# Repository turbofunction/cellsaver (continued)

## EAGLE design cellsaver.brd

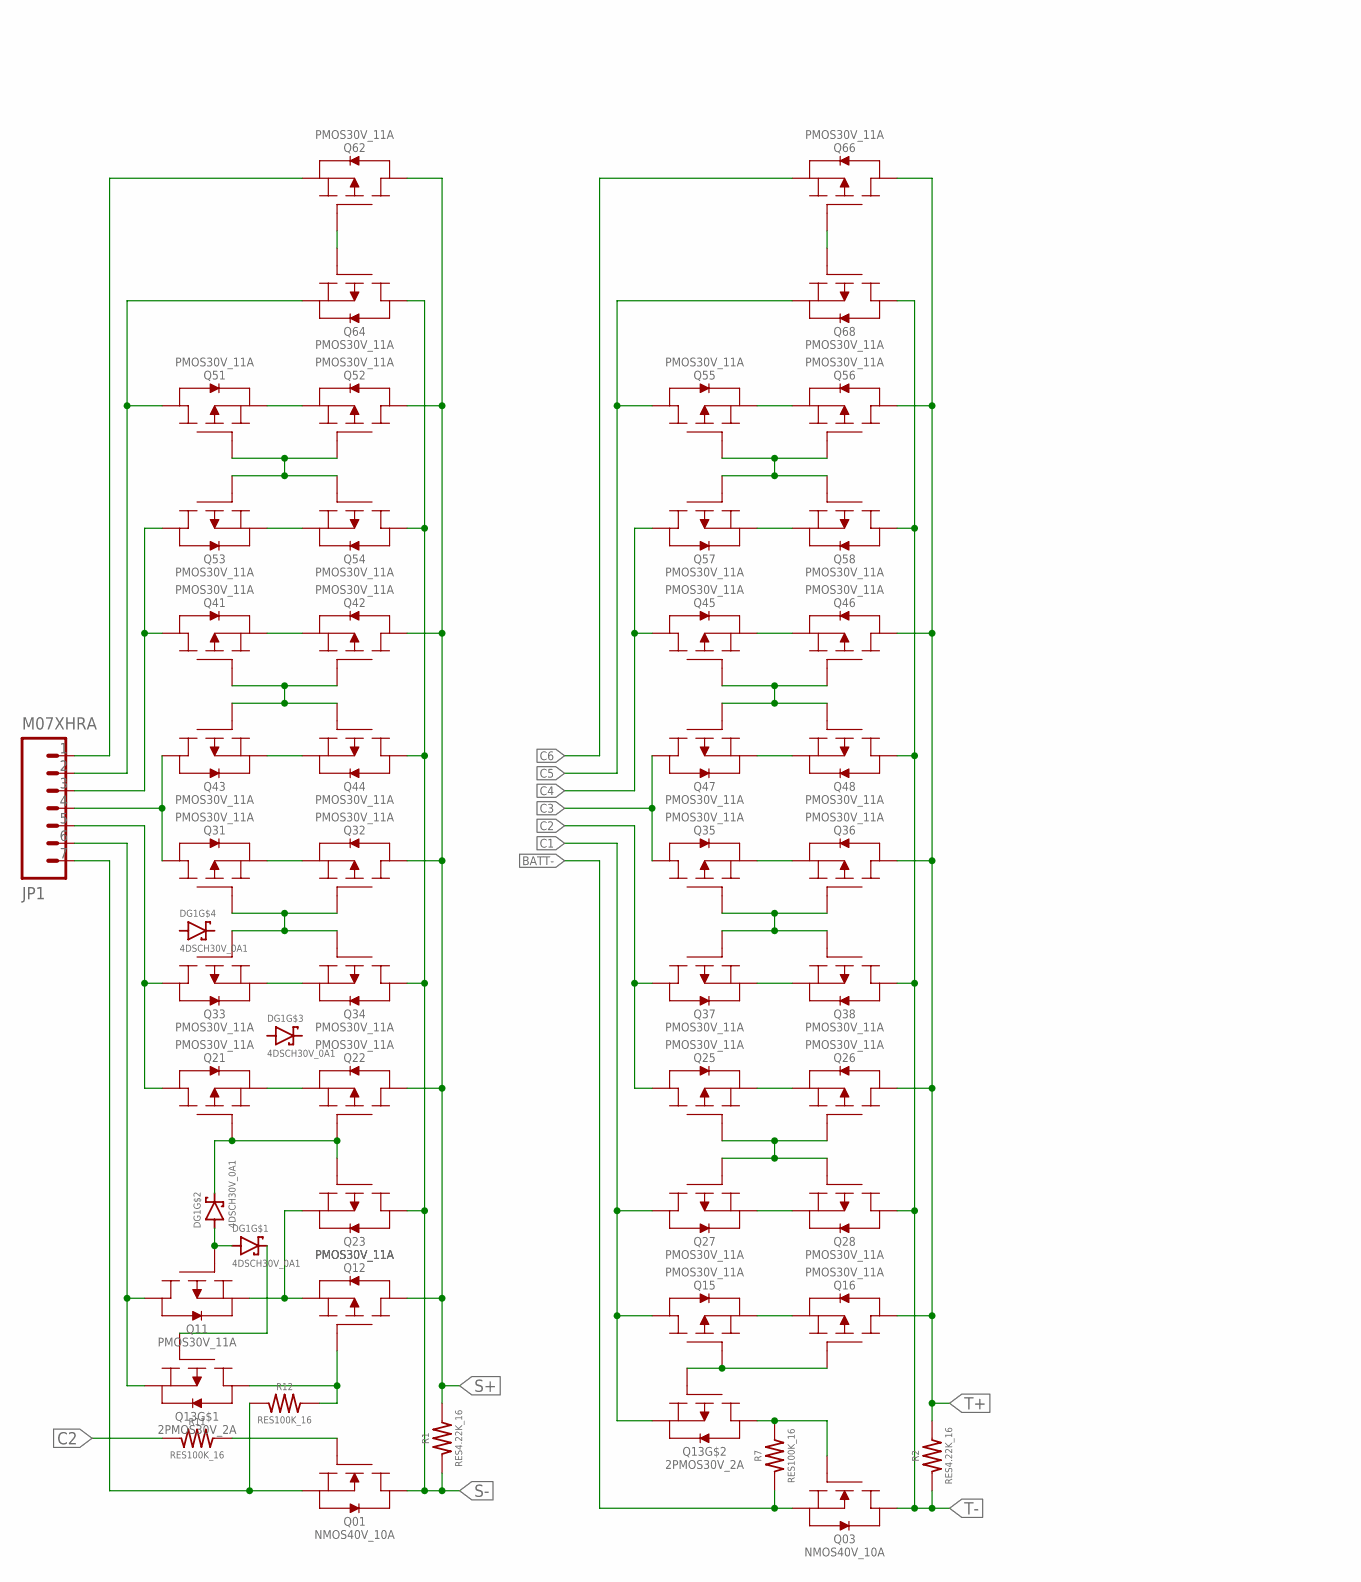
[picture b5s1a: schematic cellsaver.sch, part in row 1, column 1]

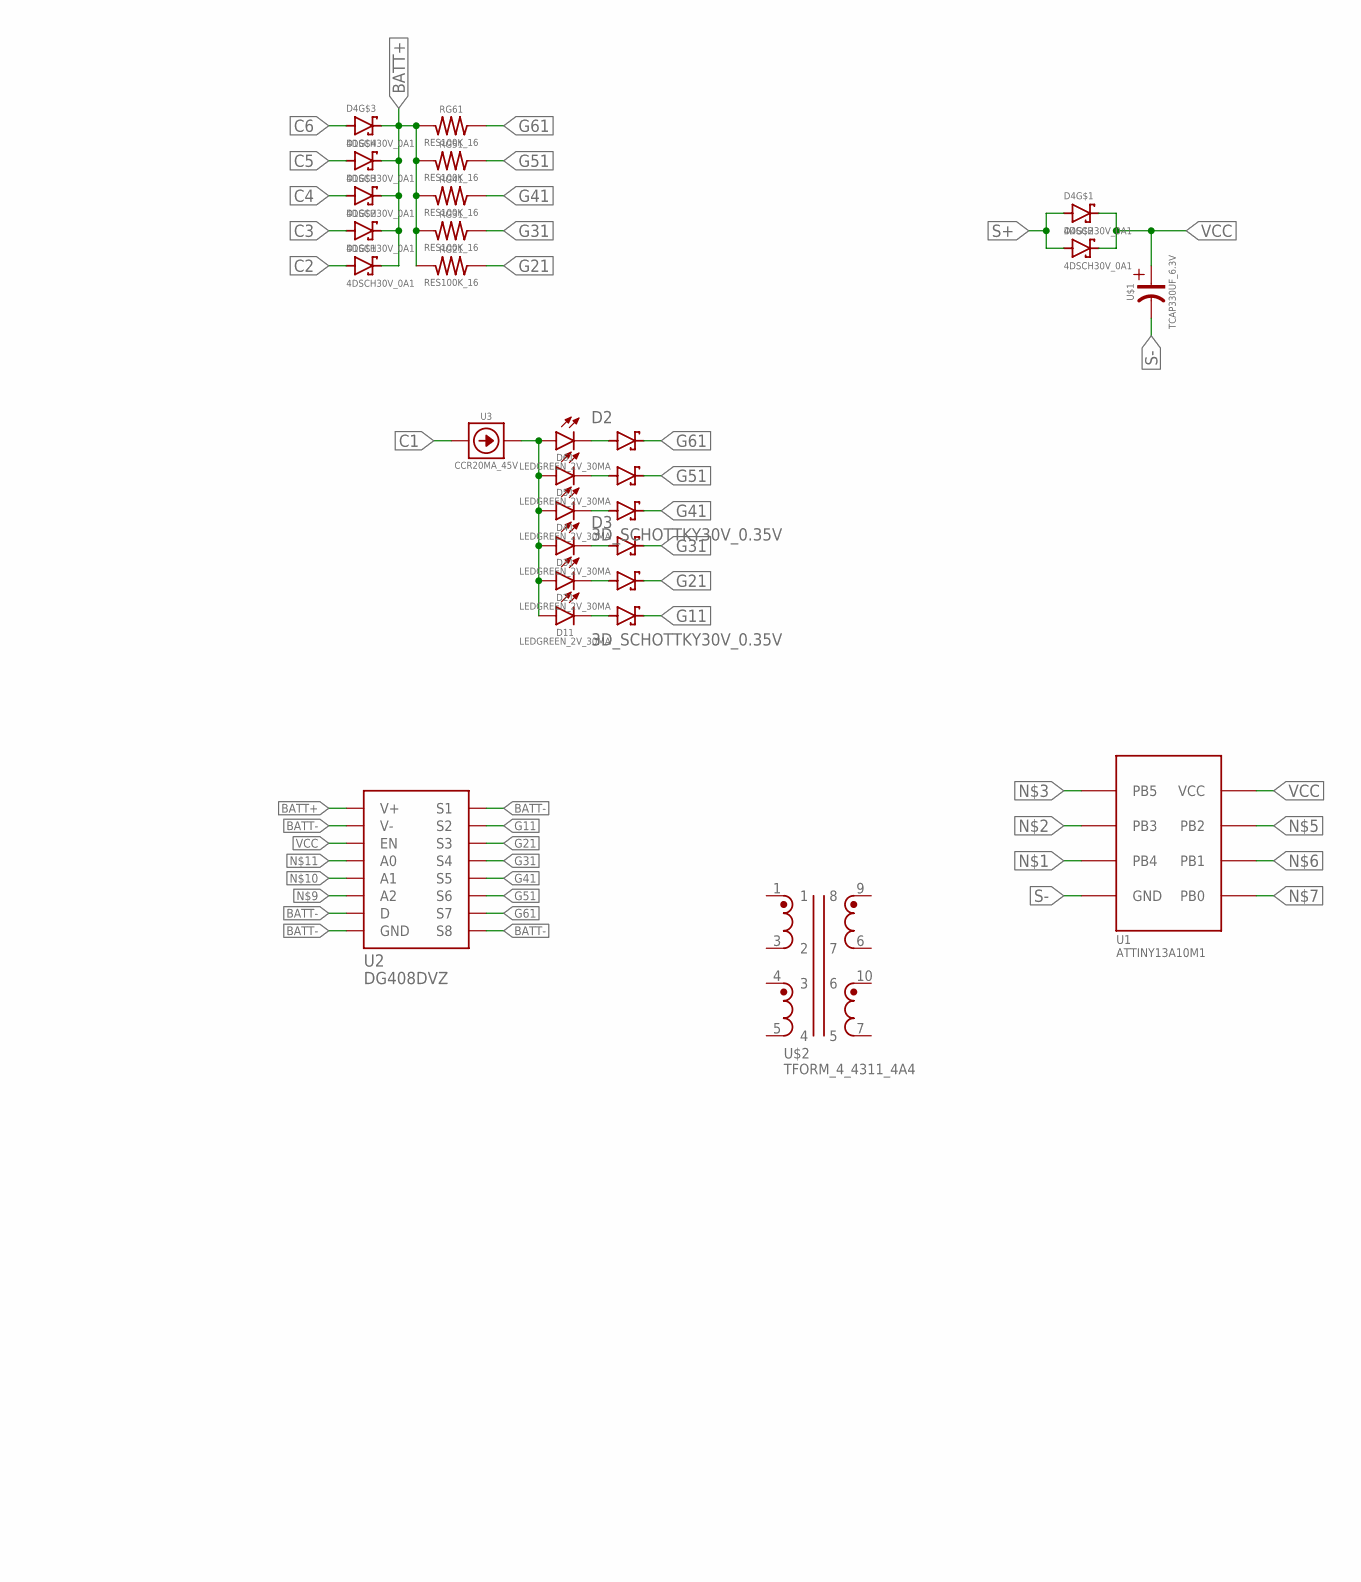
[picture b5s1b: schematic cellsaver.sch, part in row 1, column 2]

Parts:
D1, D4: 4DSCH30V_0A1; 8-HMD
D2, D3: 3D_SCHOTTKY30V_0.35V; SOT-363
D11, D21, D31, D41, D51, D61: LEDGREEN_2V_30MA; 0603+
DG1: 4DSCH30V_0A1; 8-HMD
JP1: M07XHRA; XH07-RA
Q01, Q03: NMOS40V_10A; 6-POWERWDFN
Q11, Q12, Q15, Q16, Q21, Q22, Q23, Q25, Q26, Q27, Q28, Q31, Q32, Q33, Q34, Q35, Q36, Q37, Q38, Q41, Q42, Q43, Q44, Q45, Q46, Q47, Q48, Q51, Q52, Q53, Q54, Q55, Q56, Q57, Q58, Q62, Q64, Q66, Q68: PMOS30V_11A; 6-POWERWDFN
Q13: 2PMOS30V_2A; 6-TSOP
R1, R2: RES4.22K_16; 0402
R7, R11, R12: RES100K_16; 0402
RG21, RG31, RG41, RG51, RG61: RES100K_16; 0402
U1: ATTINY13A10M1; 10-MLF
U2: DG408DVZ; 16-TSSOP
U3: CCR20MA_45V; SOD-123
U$1: TCAP330UF_6.3V; 1210+
U$2: TFORM_4_4311_4A4; EPQ13

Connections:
BATT+: D1.5 (C), D1.6 (C), D1.7 (C), D1.8 (C), D4.6 (C), RG21.1, RG31.1, RG41.1, RG51.1, RG61.1, U2.13 (V+)
BATT-: JP1.7, Q01.S, Q03.S, R7.1, R12.1, U2.4 (S1)
C1: JP1.6, Q11.D, Q13.2 (S), Q13.5 (S), Q15.D, Q27.D, U3.A
C2: D1.1 (A), JP1.5, Q21.D, Q25.D, Q33.D, Q37.D, R11.1
C3: D1.2 (A), JP1.4, Q31.D, Q35.D, Q43.D, Q47.D
C4: D1.3 (A), JP1.3, Q41.D, Q45.D, Q53.D, Q57.D
C5: D1.4 (A), JP1.2, Q51.D, Q55.D, Q64.S, Q68.S
C6: D4.3 (A), JP1.1, Q62.S, Q66.S
G02: Q03.G, Q13.4 (D), R7.2
G11: D3.4 (C3), DG1.8 (C), Q01.G, Q13.1 (G), R11.2, U2.5 (S2)
G13: Q13.3 (G), Q15.G, Q16.G
G21: D3.5 (C2), DG1.7 (C), Q21.G, Q22.G, Q23.G, RG21.2, U2.6 (S3)
G22: Q25.G, Q26.G, Q27.G, Q28.G
G31: D3.6 (C1), Q31.G, Q32.G, Q33.G, Q34.G, RG31.2, U2.7 (S4)
G32: Q35.G, Q36.G, Q37.G, Q38.G
G41: D2.4 (C3), Q41.G, Q42.G, Q43.G, Q44.G, RG41.2, U2.12 (S5)
G42: Q45.G, Q46.G, Q47.G, Q48.G
G51: D2.5 (C2), Q51.G, Q52.G, Q53.G, Q54.G, RG51.2, U2.11 (S6)
G52: Q55.G, Q56.G, Q57.G, Q58.G
G61: D2.6 (C1), Q62.G, Q64.G, RG61.2, U2.10 (S7)
G62: Q66.G, Q68.G
unnamed: D11.A, D21.A, D31.A, D41.A, D51.A, D61.A, U3.C
unnamed: D2.1 (A1), D61.C
unnamed: D2.2 (A2), D51.C
unnamed: D2.3 (A3), D41.C
unnamed: D3.1 (A1), D31.C
unnamed: D3.2 (A2), D21.C
unnamed: D3.3 (A3), D11.C
unnamed: Q12.G, Q13.6 (D), R12.2
unnamed: DG1.1 (A), DG1.2 (A), Q11.G
S+: D4.1 (A), D4.2 (A), Q12.D, Q22.D, Q32.D, Q42.D, Q52.D, Q62.D, R1.2
S+12: Q15.S, Q16.S
S+21: Q21.S, Q22.S
S+22: Q25.S, Q26.S
S+31: Q31.S, Q32.S
S+32: Q35.S, Q36.S
S+41: Q41.S, Q42.S
S+42: Q45.S, Q46.S
S+51: Q51.S, Q52.S
S+52: Q55.S, Q56.S
S-: Q01.D, Q23.D, Q34.D, Q44.D, Q54.D, Q64.D, R1.1, U1.5 (GND), U1.11 (GND), U$1.C
S-21: Q11.S, Q12.S, Q23.S
S-22: Q27.S, Q28.S
S-31: Q33.S, Q34.S
S-32: Q37.S, Q38.S
S-41: Q43.S, Q44.S
S-42: Q47.S, Q48.S
S-51: Q53.S, Q54.S
S-52: Q57.S, Q58.S
T+: Q16.D, Q26.D, Q36.D, Q46.D, Q56.D, Q66.D, R2.2
T-: Q03.D, Q28.D, Q38.D, Q48.D, Q58.D, Q68.D, R2.1
VCC: D4.7 (C), D4.8 (C), U1.10 (VCC), U2.2 (EN), U$1.A

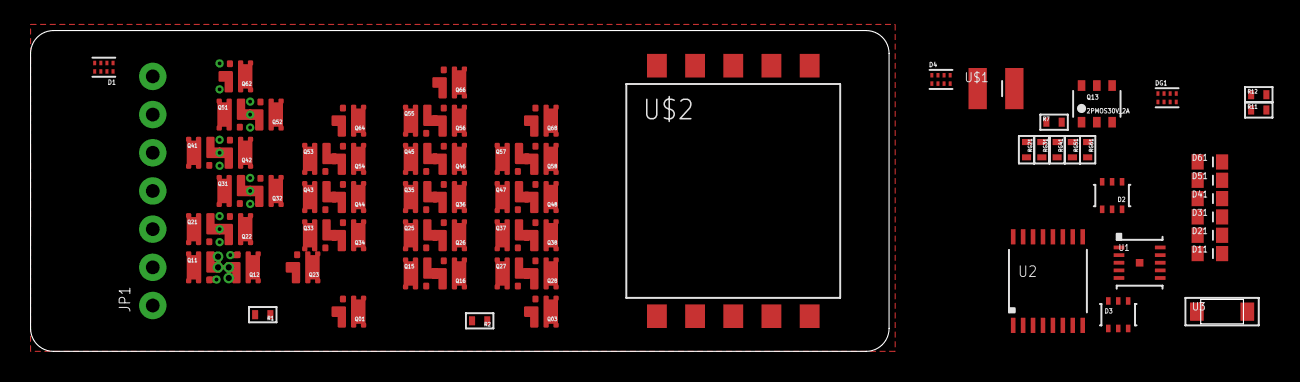
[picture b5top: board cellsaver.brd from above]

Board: 4 copper layers, 79.4 x 21.0 mm, 69 parts (0 on the bottom side), 52 nets.

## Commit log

2016-10-09 Deprecated idea of a reserve cell
2016-10-09 FET change, layout
2016-10-10 Second pair of rails, for direct contact
2016-10-10 Bootstrap power, FET optimization
2016-10-11 Transformer simulation working!
2016-10-11 Pre opto iso
2016-10-12 rename
2016-10-13 Circuit tweaks
2016-10-16 Modularizing next
2016-10-18 Switching back to an analog switch
2016-10-18 Analog switches are back
2016-10-18 Composing the schematic
2016-10-18 LTC3803 simu
2016-10-20 ltspice model good
2016-10-20 stable at high load
2016-10-20 perfect
2016-10-23 getting there
2016-10-24 starting to organize board
2016-10-24 organizing
2016-10-24 tracing
2016-10-25 laying out
2016-10-26 Removed separate S-_SENSE
2016-10-28 connectors
2016-10-28 DONE! FINISHED! VALMIS!
2016-11-02 moving boosters
2016-11-04 readme, zip script
2016-11-05 LED matrix
2016-11-08 redo
2016-11-08 jack mirror
2016-11-08 control "done"
2016-11-15 date confirmation
2016-11-16 tweaks
2016-11-16 fw template
2016-11-16 version bump
2016-11-24 Pull-downs, resistor arrays
2016-11-24 more pull-downs
2016-11-25 c1 switching fix
2016-11-25 tidy
2016-11-28 pre: remove extra switch
2016-11-29 pre: fet move
2016-11-29 rework complete
2016-11-29 wank
2016-11-30 pre: shift reg -> mcu
2016-11-30 power mcu
2016-11-30 MCU configured
2016-12-02 Moved fet
2016-12-05 neverending gilding
2016-12-09 diode conf
2016-12-25 Connector pin reordering
2016-12-25 Routing tweaks
2016-12-26 Missed a couple pmos gate pull-ups
2016-12-26 Power track paste
2016-12-26 Label fix
2016-12-27 test point
2017-08-01 LTSpice files move
2017-08-01 LT8309
2017-08-01 Inductor testing
2017-08-03 2S boost
2017-08-03 spice
2017-08-04 Inductor routing
2017-08-04 "finished"
2017-08-04 gitignore
2017-08-04 Power board finished now
2017-08-04 Compacting
2017-08-04 Compaction finished
2017-08-04 spice update
2017-08-04 Control board compacted
2017-08-04 Control board fixes
2017-08-08 Removed 2S booster
2017-08-08 Added choke
2017-08-09 routing
2017-08-09 spice models
2017-08-09 Firmware projects init
2017-08-09 prog testpoints
2017-08-09 studio confs
2017-08-09 removed lipovsky-fw template
2017-08-09 CamelCase solution names required...
2017-08-09 Better project structure
2017-08-16 ATtiny1616
2017-08-30 NMOS ref
2017-09-04 4RES pull-down; tidying
2017-09-04 Switch control pull-downs
2017-09-05 Switch pulldown routing
2017-09-05 Resistor array; tidy
2017-09-26 FET change
2017-10-03 FET footprint tweak
2017-10-03 Further FET footprint tweaking
2017-10-04 More space
2017-10-04 Feed-through cap; more space
2017-10-05 Capacitor optimization; tidy
2017-10-05 Connector update
